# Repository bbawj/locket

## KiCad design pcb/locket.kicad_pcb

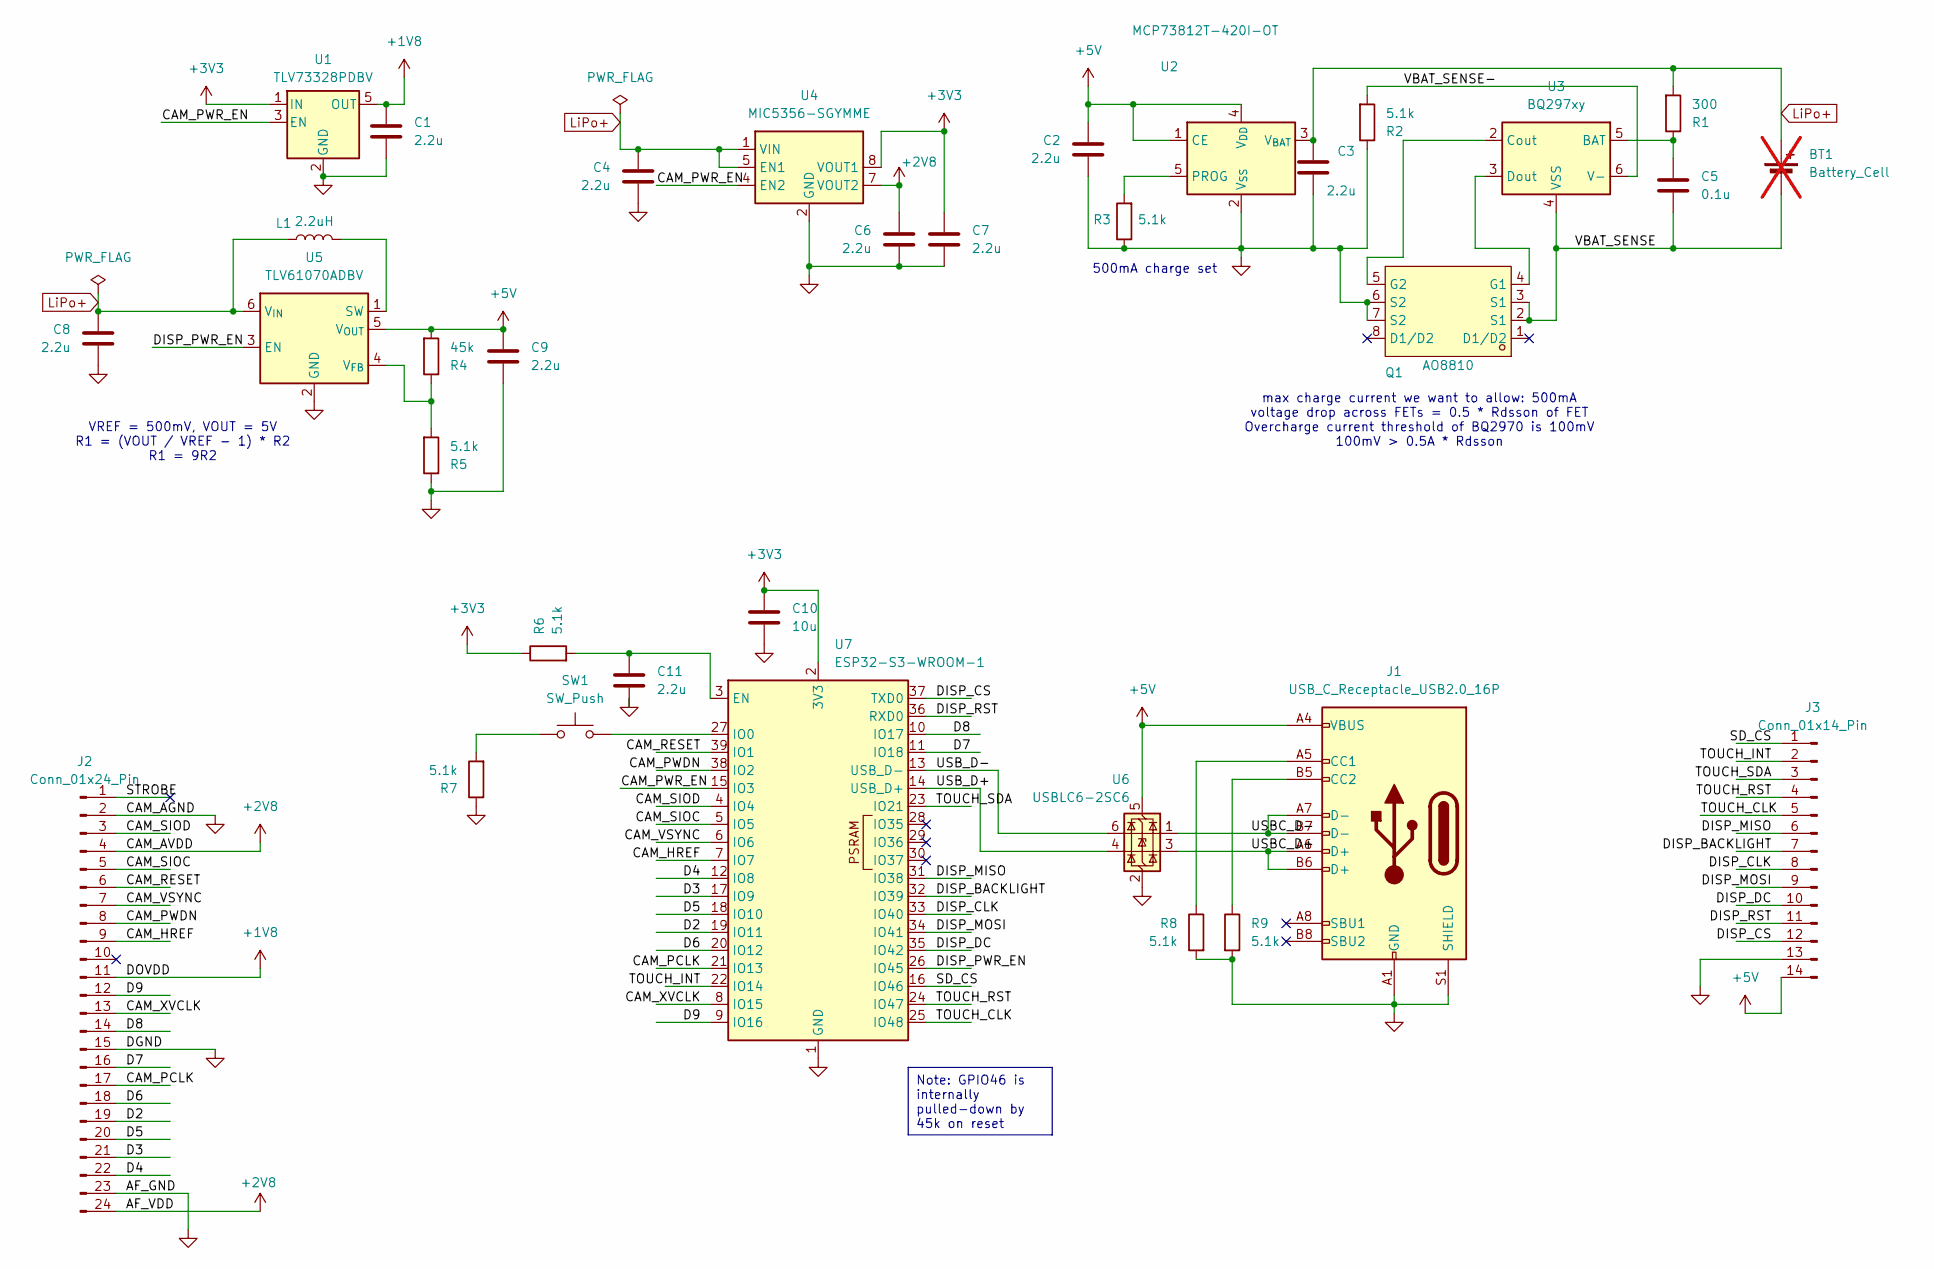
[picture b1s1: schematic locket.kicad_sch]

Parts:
BT1: Battery_Cell; JST_XH_S2B-XH-A_1x02_P2.50mm_Horizontal; not fitted
C1, C2, C3, C4, C6, C7, C8, C9, C11: 2.2u; C_0805_2012Metric
C5: 0.1u; C_0805_2012Metric
C10: 10u; C_0805_2012Metric
J1: USB_C_Receptacle_USB2.0_16P; USB_C_Receptacle_HRO_TYPE-C-31-M-12
J2: Conn_01x24_Pin; FPC-SMD_P0.50-24P_QCHF-SM-H2.0
J3: Conn_01x14_Pin; PinSocket_1x14_P2.54mm_Vertical
L1: 2.2uH; L_0805_2012Metric
Q1: AO8810; TSSOP-8_L4.4-W3.0-P0.65-LS6.4-BL; Manufacturer Part AO8810; LCSC Part Name 2个N沟道 耐压:20V 电流:7A
R1: 300; R_0805_2012Metric
R2, R3, R5, R6, R7, R8, R9: 5.1k; R_0603_1608Metric
R4: 45k; R_0805_2012Metric
SW1: SW_Push; SW_Slide_SPDT_Straight_CK_OS102011MS2Q
U1: TLV73328PDBV; SOT-23-5
U2: MCP73812T-420I-OT; SOT-23-5
U3: BQ297xy; WSON-6_1.5x1.5mm_P0.5mm
U4: MIC5356-SGYMME; MSOP-8-1EP_3x3mm_P0.65mm_EP2.5x3mm_Mask1.73x2.36mm_ThermalV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
U5: TLV61070ADBV; SOT-23-6
U6: USBLC6-2SC6; SOT-23-6
U7: ESP32-S3-WROOM-1

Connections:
+1V8: C1.1, J2.11, U1.5 (OUT)
+2V8: C6.1, J2.4, J2.24, U4.7 (VOUT2)
+3V3: C7.1, C10.1, R6.1, U1.1 (IN), U4.8 (VOUT1), U7.2 (3V3)
+5V: C2.1, C9.1, J1.A4 (VBUS), J1.A9 (VBUS), J1.B4 (VBUS), J1.B9 (VBUS), J3.14, R4.2, U2.1 (CE), U2.4 (V_{DD}), U5.5 (V_{OUT}), U6.5 (VBUS)
/CAM_HREF: J2.9, U7.7 (IO7)
/CAM_PCLK: J2.17, U7.21 (IO13)
/CAM_PWDN: J2.8, U7.38 (IO2)
/CAM_PWR_EN: U1.3 (EN), U4.4 (EN2), U7.15 (IO3)
/CAM_RESET: J2.6, U7.39 (IO1)
/CAM_SIOC: J2.5, U7.5 (IO5)
/CAM_SIOD: J2.3, U7.4 (IO4)
/CAM_VSYNC: J2.7, U7.6 (IO6)
/CAM_XVCLK: J2.13, U7.8 (IO15)
/D2: J2.19, U7.19 (IO11)
/D3: J2.21, U7.17 (IO9)
/D4: J2.22, U7.12 (IO8)
/D5: J2.20, U7.18 (IO10)
/D6: J2.18, U7.20 (IO12)
/D7: J2.16, U7.11 (IO18)
/D8: J2.14, U7.10 (IO17)
/D9: J2.12, U7.9 (IO16)
/DISP_BACKLIGHT: J3.7, U7.32 (IO39)
/DISP_CLK: J3.8, U7.33 (IO40)
/DISP_CS: J3.12, U7.37 (TXD0)
/DISP_DC: J3.10, U7.35 (IO42)
/DISP_MISO: J3.6, U7.31 (IO38)
/DISP_MOSI: J3.9, U7.34 (IO41)
/DISP_PWR_EN: U5.3 (EN), U7.26 (IO45)
/DISP_RST: J3.11, U7.36 (RXD0)
/SD_CS: J3.1, U7.16 (IO46)
/STROBE: J2.1
/TOUCH_CLK: J3.5, U7.25 (IO48)
/TOUCH_INT: J3.2, U7.22 (IO14)
/TOUCH_RST: J3.4, U7.24 (IO47)
/TOUCH_SDA: J3.3, U7.23 (IO21)
/USBC_D+: J1.A6 (D+), J1.B6 (D+), U6.3 (I/O2)
/USBC_D-: J1.A7 (D-), J1.B7 (D-), U6.1 (I/O1)
/USB_D+: U6.4 (I/O2), U7.14 (USB_D+)
/USB_D-: U6.6 (I/O1), U7.13 (USB_D-)
/VBAT_SENSE: BT1.2 (-), C5.2, Q1.2 (S1), Q1.3 (S1), U3.4 (VSS)
/VBAT_SENSE-: R2.2, U3.6 (V-)
GND: C1.2, C2.2, C3.2, C4.2, C6.2, C7.2, C8.2, C9.2, C10.2, C11.2, J1.A1 (GND), J1.A12 (GND), J1.B1 (GND), J1.B12 (GND), J1.S1 (SHIELD), J2.2, J2.15, J2.23, J3.13, Q1.6 (S2), Q1.7 (S2), R2.1, R3.1, R5.1, R7.1, R8.2, R9.2, U1.2 (GND), U2.2 (V_{SS}), U4.2 (GND), U4.9 (GND), U5.2 (GND), U6.2 (GND), U7.1 (GND), U7.40 (GND), U7.41 (GND)
LiPo+: BT1.1 (+), C3.1, C4.1, C8.1, L1.1, R1.2, U2.3 (V_{BAT}), U4.1 (VIN), U4.5 (EN1), U5.6 (V_{IN})
unnamed: J1.A5 (CC1), R8.1
unnamed: J1.B5 (CC2), R9.1
unnamed: Q1.4 (G1), U3.3 (Dout)
unnamed: Q1.5 (G2), U3.2 (Cout)
unnamed: R7.2, SW1.1
unnamed: R3.2, U2.5 (PROG)
unnamed: C5.1, R1.1, U3.5 (BAT)
unnamed: L1.2, U5.1 (SW)
unnamed: R4.1, R5.2, U5.4 (V_{FB})
unnamed: C11.1, R6.2, U7.3 (EN)
unnamed: SW1.2, U7.27 (IO0)

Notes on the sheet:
Note: GPIO46 is internally pulled-down by 45k on reset
max charge current we want to allow: 500mA voltage drop across FETs = 0.5 * Rdsson of FET Overcharge current threshold of BQ2970 is 100mV 100mV > 0.5A * Rdsson
500mA charge set
VREF = 500mV, VOUT = 5V R1 = (VOUT / VREF - 1) * R2 R1 = 9R2

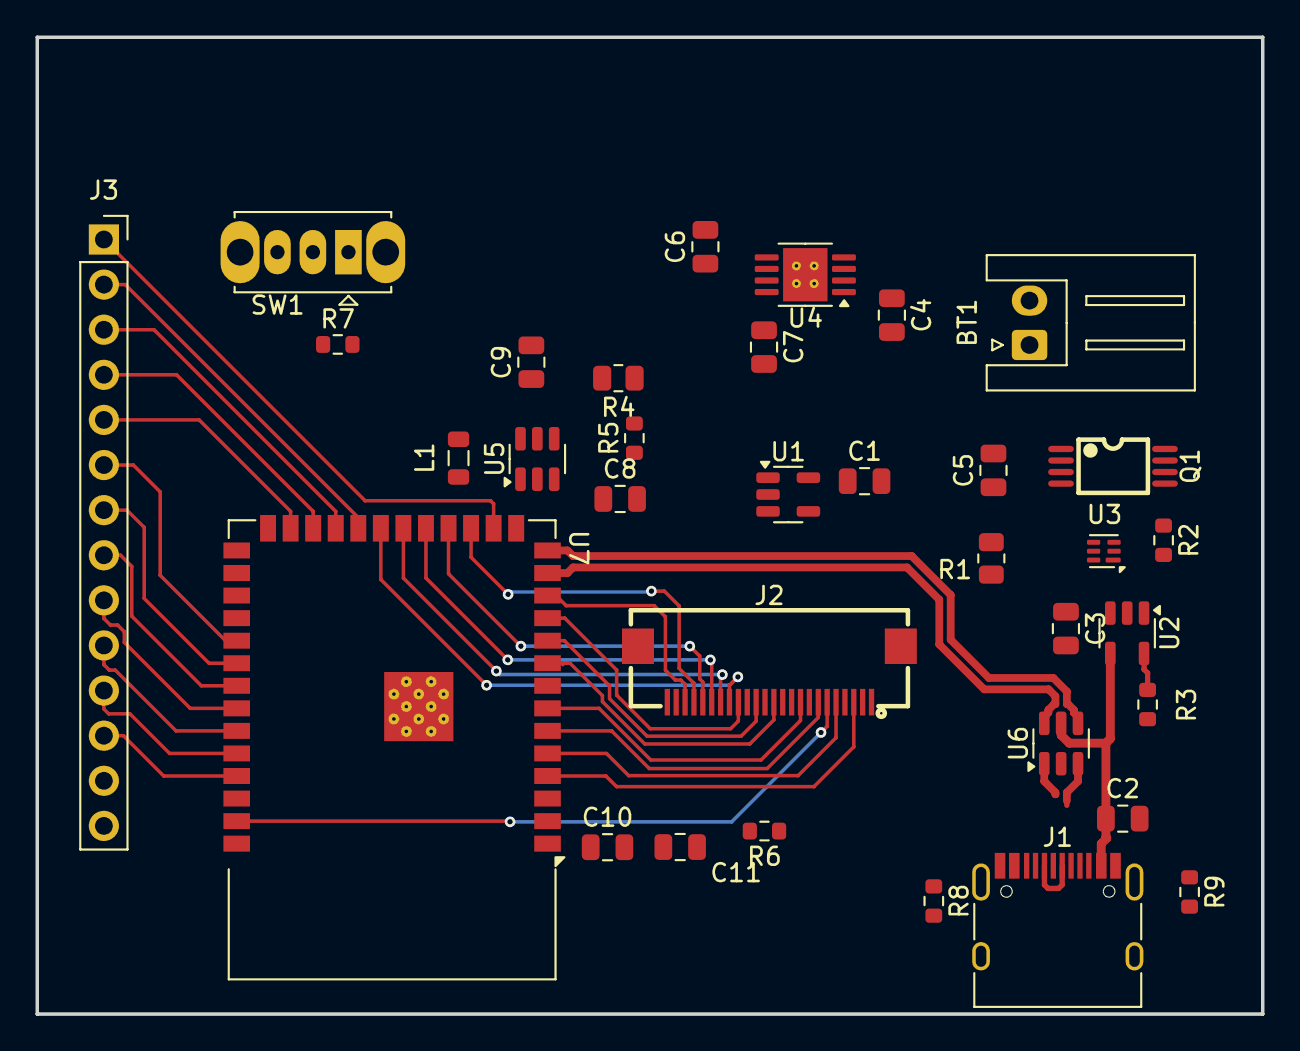
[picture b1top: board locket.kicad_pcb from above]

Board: 2 copper layers, 69.0 x 55.0 mm, 34 parts (0 on the bottom side), 53 nets.

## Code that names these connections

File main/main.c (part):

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#define EXAMPLE_PIN_NUM_CS 38
#define EXAMPLE_PIN_NUM_RST 39
#define EXAMPLE_PIN_NUM_DC 40
#define DISP_MOSI 41
#define EXAMPLE_PIN_NUM_PCLK 42
#define EXAMPLE_PIN_NUM_BK_LIGHT 43
#define DISP_MISO 44

#define TOUCH_RST 14
#define TOUCH_INT 21
#define TOUCH_SCL 47
#define TOUCH_SDA 48

// The pixel number in horizontal and vertical
#define EXAMPLE_LCD_H_RES 480
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    assert(s_lines[i] != NULL);
  }

  gpio_config_t touch_rst = {.mode = GPIO_MODE_OUTPUT,
                             .pin_bit_mask = 1ULL << TOUCH_RST};
  ESP_ERROR_CHECK(gpio_config(&touch_rst));

  gpio_config_t touch_int = {
      .mode = GPIO_MODE_INPUT,
      .pin_bit_mask = 1ULL << TOUCH_INT,
      .intr_type = GPIO_INTR_NEGEDGE,
  };
  ESP_ERROR_CHECK(gpio_config(&touch_int));

  i2c_master_bus_config_t i2c_mst_config = {
      .clk_source = I2C_CLK_SRC_DEFAULT,
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    //   break;
    // }

    gpio_intr_disable(TOUCH_INT);
    handle_touch_event(&touch_handle, &e);
    switch (state) {
    case Display: {
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    case CameraPreview:
      break;
    }
    gpio_intr_enable(TOUCH_INT);
    vTaskDelay(10 / portTICK_PERIOD_MS);
  }
  // free(camera_image);
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
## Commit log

2025-01-11 init
2025-02-11 laptop charger is dead
2025-02-23 schematic final and starting layout
